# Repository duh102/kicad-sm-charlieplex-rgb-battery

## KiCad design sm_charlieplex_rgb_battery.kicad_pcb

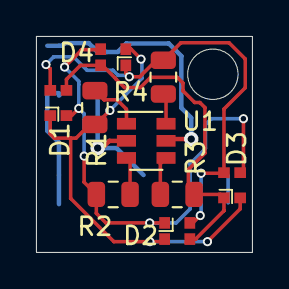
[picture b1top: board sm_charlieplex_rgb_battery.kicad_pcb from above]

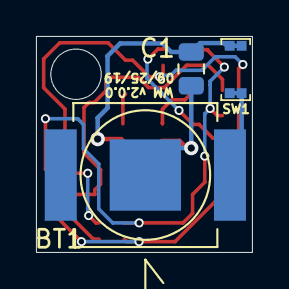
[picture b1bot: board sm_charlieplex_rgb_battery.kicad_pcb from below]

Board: 2 copper layers, 12.0 x 12.0 mm, 12 parts (3 on the bottom side), 11 nets.

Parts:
BT1: Battery_Cell; BatteryHolder_Keystone_2998_621_6.8x2.2mm
C1: 4.7uF; C_0805_2012Metric
D1, D2, D3, D4: LED_BGRA; LED_RGB_EAST1616RGBA3
R1, R2, R3, R4: 100R; R_0805_2012Metric
SW1: SW_Push; SW_Push_2.6x1.6x0.53mm_EVP-BB2A9B000
U1: ATtiny10-TS; SOT-23-6

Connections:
/+3V: BT1.1, SW1.1
/GND: BT1.2, C1.2, U1.2
unnamed: C1.1, SW1.2, U1.5
unnamed: D1.1, D2.1, D3.1, D4.4, R4.1
unnamed: D1.2, D2.2, D3.4, D4.1, R3.1
unnamed: D1.3, D2.4, D3.2, D4.2, R2.1
unnamed: D1.4, D2.3, D3.3, D4.3, R1.1
unnamed: R1.2, U1.1
unnamed: R2.2, U1.3
unnamed: R3.2, U1.4
unnamed: R4.2, U1.6

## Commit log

2019-09-25 Finish routing
2019-09-25 Bump version on board
2019-09-26 Move date text slightly
